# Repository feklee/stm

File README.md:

Introduction
============

Software and hardware source code for a DIY STM being developed at Fab Lab
Berlin.

For documentation, see: <https://wiki.fablab.berlin/index.php/STM>

Coding conventions
==================

  * Maximum line length: 80 characters

  * Comments in Markdown

  * JavaScript passes JSLint.

Thanks
======

  * [Dan Berard][4]: lots of suggestions by email, detailed documentation of
    his STM project

  * [hackerspaceshop][1]: donation of Teensy bluetooth serial module

  * [HU Berlin][2]: donation of graphite, platinum-iridium tips

  * [SparkMaker][3]: funding for parts

Legal
=====

Unless mentioned otherwise, stuff is licensed under the WTFPL version 2:
<http://www.wtfpl.net/>

[1]: https://hackerspaceshop.com/
[2]: https://www.hu-berlin.de/
[3]: http://sparkmaker.io/
[4]: https://dberard.com/

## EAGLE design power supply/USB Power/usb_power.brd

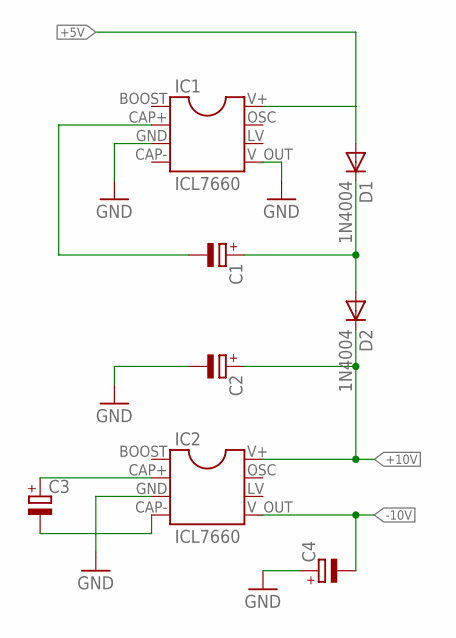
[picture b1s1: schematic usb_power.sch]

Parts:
C1, C2, C3, C4: CPOL-EUE2-4; E2-4
D1, D2: 1N4004; DO41-10
IC1, IC2: ICL7660; DIL08

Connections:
+5V: D1.A, IC1.V+ (8)
+10V: C2.+, D2.C, IC2.V+ (8)
-10V: C4.-, IC2.V_OUT (5)
GND: C2.-, C4.+, IC1.GND (3), IC1.V_OUT (5), IC2.GND (3)
unnamed: C1.-, IC1.CAP+ (2)
unnamed: C1.+, D1.C, D2.A
unnamed: C3.+, IC2.CAP+ (2)
unnamed: C3.-, IC2.CAP- (4)

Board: 2 copper layers, 8 parts (0 on the bottom side), 8 nets, no tracks yet.

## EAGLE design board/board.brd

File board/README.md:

Layout for a board for controlling the STM.

The source of Teensy 3.x component is an Eagle library linked from a post
[Updated Teensy 3.x and LC Eagle libraries][1] in the PJRC forum.

[1]: https://forum.pjrc.com/threads/24637-Updated-Teensy-3-1-and-Teensy-3-0-Eagle-libraries?p=38388&viewfull=1#post38388

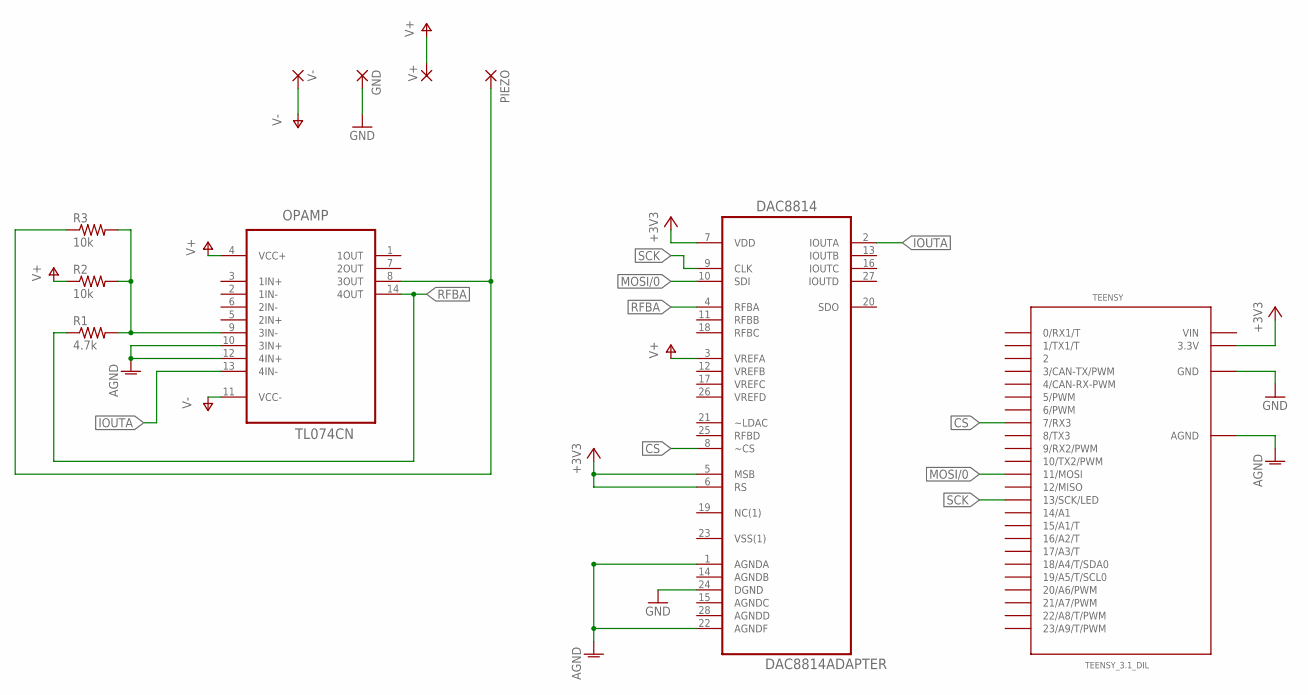
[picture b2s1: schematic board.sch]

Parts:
DAC8814: DAC8814ADAPTER; DIL28-6
GND: 1,6/0,8
OPAMP: TL074CN; DIP254P762X508-14
PIEZO: 1,6/0,8
R1: 4.7k; 0204/7
R2, R3: 10k; 0204/5
TEENSY: TEENSY_3.1_DIL; TEENSY3-DIL
V+: 1,6/0,8
V-: 1,6/0,8

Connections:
+3V3: DAC8814.5 (MSB), DAC8814.6 (RS), DAC8814.7 (VDD), TEENSY.3.3V
AGND: DAC8814.1 (AGNDA), DAC8814.22 (AGNDF), OPAMP.10 (3IN+), OPAMP.12 (4IN+), TEENSY.AGND
CS: DAC8814.8 (~CS), TEENSY.7 (7/RX3)
GND: DAC8814.24 (DGND), GND.1, TEENSY.GND
IOUTA: DAC8814.2 (IOUTA), OPAMP.13 (4IN-)
MOSI/0: DAC8814.10 (SDI), TEENSY.11 (11/MOSI)
unnamed: OPAMP.9 (3IN-), R1.2, R2.2, R3.2
unnamed: OPAMP.8 (3OUT), PIEZO.1, R3.1
RFBA: DAC8814.4 (RFBA), OPAMP.14 (4OUT), R1.1
SCK: DAC8814.9 (CLK), TEENSY.13 (13/SCK/LED)
V+: DAC8814.3 (VREFA), OPAMP.4 (VCC+), R2.1, V+.1
V-: OPAMP.11 (VCC-), V-.1
VIN: TEENSY.VIN

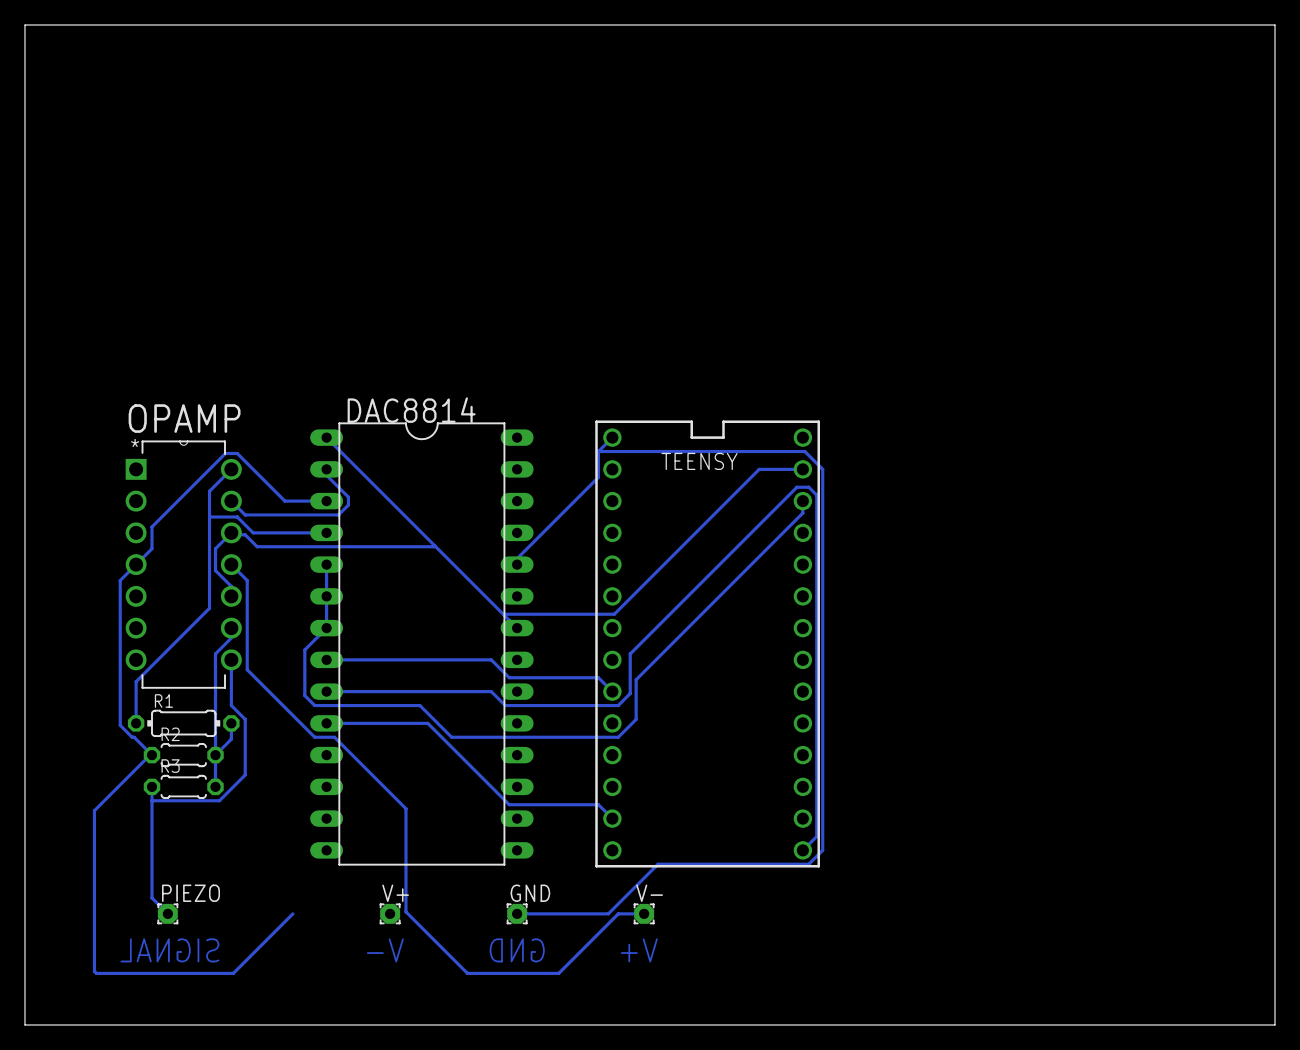
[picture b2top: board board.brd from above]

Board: 2 copper layers, 100.0 x 80.0 mm, 10 parts (0 on the bottom side), 12 nets.

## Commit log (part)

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2015-10-22 Add test code
2015-10-22 Add documentation
2015-10-22 Tweak
2015-10-22 Added mechanics plans
2015-10-22 Add link to wiki
2015-10-22 Rename test to approach
2015-10-22 Tweaks
2015-10-24 Add new top plate; Update code (CLI)
2015-10-27 Add piezo
2015-11-08 Add output of measurements during approach
2015-11-08 Add instructions how to plot with Gnuplot
2015-11-12 Add code for setting bias voltage (not functional)
2015-11-12 Use SPI library (untested)
2015-11-13 Add TINA opamp circuit schema
2015-11-14 Change chip select pin; Remove unneeded schema
2015-11-14 Add command to set bias voltage
2015-11-15 Add John Alexander's preamp
2015-11-15 Add voltage divider
2015-11-15 Simulate gap by resistor
2015-11-15 Update voltage scaling; Replace opamp
2015-11-16 Add alternative preamp circuit (untested)
2015-11-16 Add voltage inversion to John's circuit
2015-11-16 Add inversion of signal
2015-11-16 Mark my too primitive scheme as experimental
2015-11-17 Add RC filter
2015-11-17 Change default bias voltage to 50 mV
2015-11-17 Add command to play sound to test piezo
2015-11-18 Speed up piezo move if single stepping not needed
2015-11-18 Introduce separate single step function
2015-11-19 Add monitoring of signal (untested)
2015-11-19 Add fixes (still bugs with logging)
2015-11-20 Fix: monitoring should not log
2015-11-20 Fix syntax
2015-11-20 Increase speed for serial communication
2015-11-20 Allow specification of piezo step size
2016-01-15 Always show log of last signals; Fix wp approach
2016-01-15 Remove continuous signal log facility
2016-01-16 Measure duration of cmnds; Add silent monitoring
2016-01-17 Add delay to dampen SPI noise
2016-01-28 Add PC interface; Improce mechanics; Reorder files
2016-01-28 Processing tool: wider dropdown
2016-01-28 Fix: Monitored signal not printed correctly
2016-01-28 Reorder functions for compiler compatibility
2016-01-31 Fix: Output of signals and tagging
2016-01-31 Fix: missing separator
2016-02-04 New mechanics design for 3 mm acrylics
2016-02-04 Simplify design for easier & more precise cutting
2016-02-06 Add basic drawings for mech, as requested by Luka
2016-02-09 Clean up; Start with wiring diagram
2016-02-09 Changed rubber band mount
2016-02-09 Update wiring diagram
2016-02-12 Change drawing mode, update wiring
2016-02-12 Remove delay after positioning piezo
2016-02-12 Changed font back, for performance reasons
2016-02-12 Let piezo move up at end of woodpecker approach
2016-02-13 Add clear button
2016-02-22 Update documentation
2016-03-13 Fix order of gui element creation
2016-03-20 Fix: Serial port menu obscured
2016-03-27 Documentation for switch of piezo controller
2016-04-09 2016-04-09_electronics pictures
    On the new dac breadboard: moved 2 cables up, making space for second op amp.
    This is needed for "bipolar output". In the datasheet of the DAC 8814, the
    needed circuit is described on p. 21. (For non-multiplying DACs only one op is
    needed)
2016-04-09 piezotest: remove unused code
2016-04-13 Add support for new DAC; Screenshot of new circuit
2016-04-17 Add piezo position to signal log; Start with hover
2016-04-17 Add transistor to turn motor on/off
2016-04-17 Add photos of current setup
2016-04-24 Simplify approach
2016-04-24 Start adding web frontend
2016-04-24 Implement hovering
2016-04-25 Rename to avoid confusion; Tweak aproach
2016-04-25 Fix issues
2016-04-25 Update coding conventions
2016-05-15 Piezo Test: defines for DAC ports
2016-05-15 Using DAC channel 0 as old DAC is removed
2016-05-21 Change Motor activation from fried pin 10 => 9
2016-05-24 Approach again with higher resolution, then hover
2016-05-24 Add draft for video installation
2016-06-04 Visualize beam; Speed up scanning
2016-06-04 Remove express
2016-06-06 Bundle pixels when sent over WebSockets
2016-06-06 Simplify: Remove protocol name
2016-06-06 Read simulated image from file
2016-06-06 Introduce mixer
2016-06-06 Speed up
2016-06-07 Add serial port communication
2016-06-08 10V => 3V - Tina Schematics
2016-06-09 Add scan
2016-06-09 Move simulation to Teensy
2016-06-09 Remove old simulator
2016-06-09 Fix: z not randomly walking
2016-06-09 Add interface for fader
2016-06-09 Increase serial data rate
2016-06-09 Add interface to remotely start scan
2016-06-10 Refactor modes into separate classes
2016-06-10 Stop scan from automatically repeating
2016-06-10 Pass side length from server
2016-06-10 Add proper error handling; Make fader more robust
2016-06-10 Change position log infrastructure
2016-06-10 Remove debugging output
2016-06-10 Add missing files
2016-06-10 Add rudimentary code for graph
2016-06-10 Update naming
2016-06-11 Add ideas; Tweaks
2016-06-11 Just a note
2016-06-11 Introduce timestamp
2016-06-11 Remove timestamp
2016-06-11 Add reporting of scan duration
2016-06-11 Smaller buffer size so serial port doesn't disappear
2016-06-11 Remove logging from once per loop
2016-06-11 Fix: Duration calculation wrong with overflow
2016-06-11 Speed up serialization of positions
2016-06-11 Speed up by scanning in chunks
2016-06-11 Fix: z position only updated once per chunk
2016-06-11 Smoothen drawing animation
2016-06-12 Add drawing of vertical z graph
2016-06-12 Single graph -> multiple graphs
2016-06-12 Add delay to idle mode; New idea
2016-06-12 Align all graphs
2016-06-12 Separate mode classes into dedicated files
2016-06-12 Add approach mode
2016-06-12 Move pin declaration into class
2016-06-12 Implement motor control
2016-06-12 Implement reading of signal
2016-06-12 Add bias voltage control
2016-06-12 Fix: Bias voltage not correctly measured
2016-06-12 Make approach with motor work
2016-06-12 Add retract mode
2016-06-12 Use idle mode as successor for every mode
2016-06-12 Set width to 16:9 times height
2016-06-12 Let static files be server by server
2016-06-13 Add default definitions for basic functions
2016-06-13 Add piezo control
2016-06-13 Add piezoPlay mode
2016-06-13 Simplify starting of server
2016-06-13 Clarify: Position -> TipPosition
2016-06-13 Change also on server: position -> tip position
2016-06-13 Simplify approach and retract modes
2016-06-13 Fix approach, retract
2016-06-14 Clarify code structure
2016-06-14 Remove what is done
2016-06-14 Fix: build errors
2016-06-14 Make signal comparison easier to understand
2016-06-14 Implement woodpecker approach
2016-06-14 Update naming; Add current log to retract mode
2016-06-14 Replace current log by tip position log
2016-06-14 Retract with piezo prior to retracting with motor
2016-06-14 Add message on mode switch
2016-06-14 Add chaining of modes
2016-06-14 Add ideas
2016-06-14 Make server compatible with new firmware
2016-06-14 Differentiate data preparation by mode
2016-06-14 Continue on idle mode
2016-06-14 Fix: Continuous sequence doesn't show
2016-06-14 Mix in current signal instead of z
2016-06-14 Add idea
2016-06-15 Simplify: ModeQueue → ModeChain
2016-06-15 boolean → bool
2016-06-15 Implement basic constant current mode (tip adj.)
2016-06-15 Fix: Sometimes bad JSON with values 0.0.01 for ex.
2016-06-15 Fix delta displacement, STM error reporting
2016-06-15 Tweak output
2016-06-15 Switch back to constant height mode
2016-06-15 Make target current signal configurable
2016-06-15 Make piezo step size configurable
2016-06-15 Report peak signals during approach
2016-06-15 targetCurrentSignal → targetSignal
2016-06-18 Compute simulated scan; Tweak
2016-06-18 Fix: Image module not found anymore
2016-06-20 Change order of motor pins
2016-06-20 Adapt bias voltage to 3.3 V
2016-06-21 Woodpecker: Target piezo position to middle
2016-06-21 Remove outdated idea
2016-06-21 Named args => if ...
2016-06-21 Fix serialport for Raspi (2.1.0 => 3.1.2)
    Here somewhere it says "Update serialport to 3.1.1"; others
    reproduce problem with 2.x
2016-06-23 Add web app configuration; Tweak
2016-06-23 Add canvas performance improvements
2016-06-23 Speed up: Scale canvas using CSS transforms
2016-06-23 Update browser configuration
    See: <https://developer.vieraconnect.com/dev-guide/html5-v2.0/developmen
    t-guide/browser-configuration>
2016-06-23 Remove red testing background
2016-06-23 Change IP of web socket
2016-06-23 Reverse action of fader
2016-06-23 Remove debugging noise
2016-06-23 Adjust target signal
2016-06-23 Update transition duration
2016-06-24 Remove scaling of image canvas
2016-06-24 Simulate scanning in server
2016-06-24 Tweak simulation parameters
2016-06-24 Fix flushing (approach, retract); Speed up
2016-06-24 Remove random measurement
2016-06-25 Tweak draw rate
2016-06-25 Speed: Revert to scaling up of image&beam canvases
2016-06-25 Add optional data log
2016-06-26 Wiki link
2016-07-05 Switch direction of fader
2016-07-08 Fix: Fader position 0 not handled correctly
2016-07-08 Make compatible with latest JSLint
2016-07-08 Make compatible with JSLint 2016-06-27
2016-08-24 Add photo of installation
2016-08-30 Remove video installation
2016-08-30 Reuse microcontroller code from video installation
2016-08-30 Remove outdated information
2016-09-01 Add input for commands, and interpretation
2016-09-01 Make naming consistent
2016-09-01 Name button more clearly
2016-09-01 Add D3
2016-09-01 Fix: D3 not loaded from correct location
2016-09-02 Remove mixer
2016-09-02 Add graph
2016-09-02 Add second graph
2016-09-03 Add more info
2016-09-03 Restructure HTML
2016-09-03 Output scan duration
2016-09-03 Add reporting of peak signals after approach
2016-09-03 Add error messages to log
2016-09-03 Convert log to list
2016-09-04 Prettify input form
2016-09-04 Make input nicer
2016-09-04 Move to compass for CSS
2016-09-04 Add resizable split pane
2016-09-04 Remove SASS cache
2016-09-04 Make form layout fluid
2016-09-04 Implement zooming restricted along x
2016-09-04 Make vertical alignment work in input log
2016-09-04 Tweak resizing
2016-09-04 Make graph scaling work
2016-09-04 Clean up borders
2016-09-04 Make word wrap work in Firefox as well
2016-09-05 Make log linebreak work nicely in Firefox
2016-09-05 Make graph resize be detected on split pane resize
2016-09-05 Set up Bower with a font as first package
2016-09-05 Move D3 to Bower
2016-09-05 Moved to using ReqiureJS from Bower
2016-09-05 Specify fonts
2016-09-05 Adjust font sizes
2016-09-05 Pretty print JSON
2016-09-05 Adjust initial size of input pane
2016-09-05 Brighten background of graphs
2016-09-05 Use D3 for simplicity
2016-09-06 Add draft of board layout
2016-09-08 Add and arrange components for controlling piezo
2016-09-08 Add missing connections
2016-09-08 Remove fader
2016-09-08 Move to integer arithmetic for signals
2016-09-09 Made retract mode more stable
2016-09-09 Fix: didn't compile
2016-09-09 Output target signal to frontend
2016-09-09 Remove target signal from frontend
2016-09-09 Add missing utilities
2016-09-09 Mention SparkMaker
2016-09-09 Add link
2016-09-09 Take target signal in V again
2016-09-09 Arrange info items in horizontal lists
2016-09-09 Move to pure SCSS
2016-09-09 Add CSS reset
2016-09-09 Add stop button; Fix SCSS UTF-8 issue
2016-09-10 Make line width in graph not scale
2016-09-10 Rename to make clear that STM is the whole
2016-09-10 Update i-symbol
2016-09-10 Light blue → light gray
2016-09-10 Simplify messages
2016-09-10 USB power schematics
2016-09-10 Pass serial port messages to browser
2016-09-10 Make logging more fine grained
2016-09-10 Introduce warning messages
2016-09-10 Report bad microcontroller data to frontend
2016-09-10 Reword error message
2016-09-11 Update positioning
2016-09-11 Add spacing
2016-09-11 Reduce spacing between sections
2016-09-11 Separate heading clearer
2016-09-11 Make main pane scroll on overflow
2016-09-11 Append data to graphs
2016-09-12 Remove zoom functionality (broken)
2016-09-12 Clean up
2016-09-12 Retrieve side length from microcontroller
2016-09-12 Add axis for current signal
2016-09-12 Fix: axes not correctly positioned on rescale
2016-09-13 Make graphs zoom and panable
2016-09-13 Add strech controls
2016-09-13 Add proper captions
2016-09-13 Add spacing around headings
2016-09-13 Remove data for testing
2016-09-13 Log time
2016-09-13 Scale x-axis to microseconds
2016-09-14 Simplify
2016-09-14 Add fit width button
2016-09-14 Enable new features for scan and retract
2016-09-14 Increase log size
2016-09-15 Improve graph update performance
2016-09-15 Add coordinate display
